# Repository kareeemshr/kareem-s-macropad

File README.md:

# kareem-s-macropad
My own macro pad to use to boost my coding productivity also my first actual project involving pcb's and 3d printed parts
im not really good at naming stuf so here my name :) even tho the macropads ugly i still made it, it has 12 switches(including that of the rotary encoder) along with a 128x32 OLED display and a ec11 rotary encoder

**CAD MODEL**

**BOTTOM OF THE CASE**

**TOP OF THE CASE**

**PCB SCHEMATICS**

(ik it looks ugly but its my first time T-T)
**PCB**

**FIRMWARE**
for the firmware i just made it so that all the keys write letters,ill actually make them do something when/if i get the hardware(no the rotary encoder doesnt do anything for now other than its button writing a letter)

**this is all just three days of work with literally 0 experience before so like if it wasnt obvious now u know**

**BOM**
1x xiao rp2040
11x cherry mx switches 
1x ec11 rotary encoder
1x 0.91 128x32 OLED

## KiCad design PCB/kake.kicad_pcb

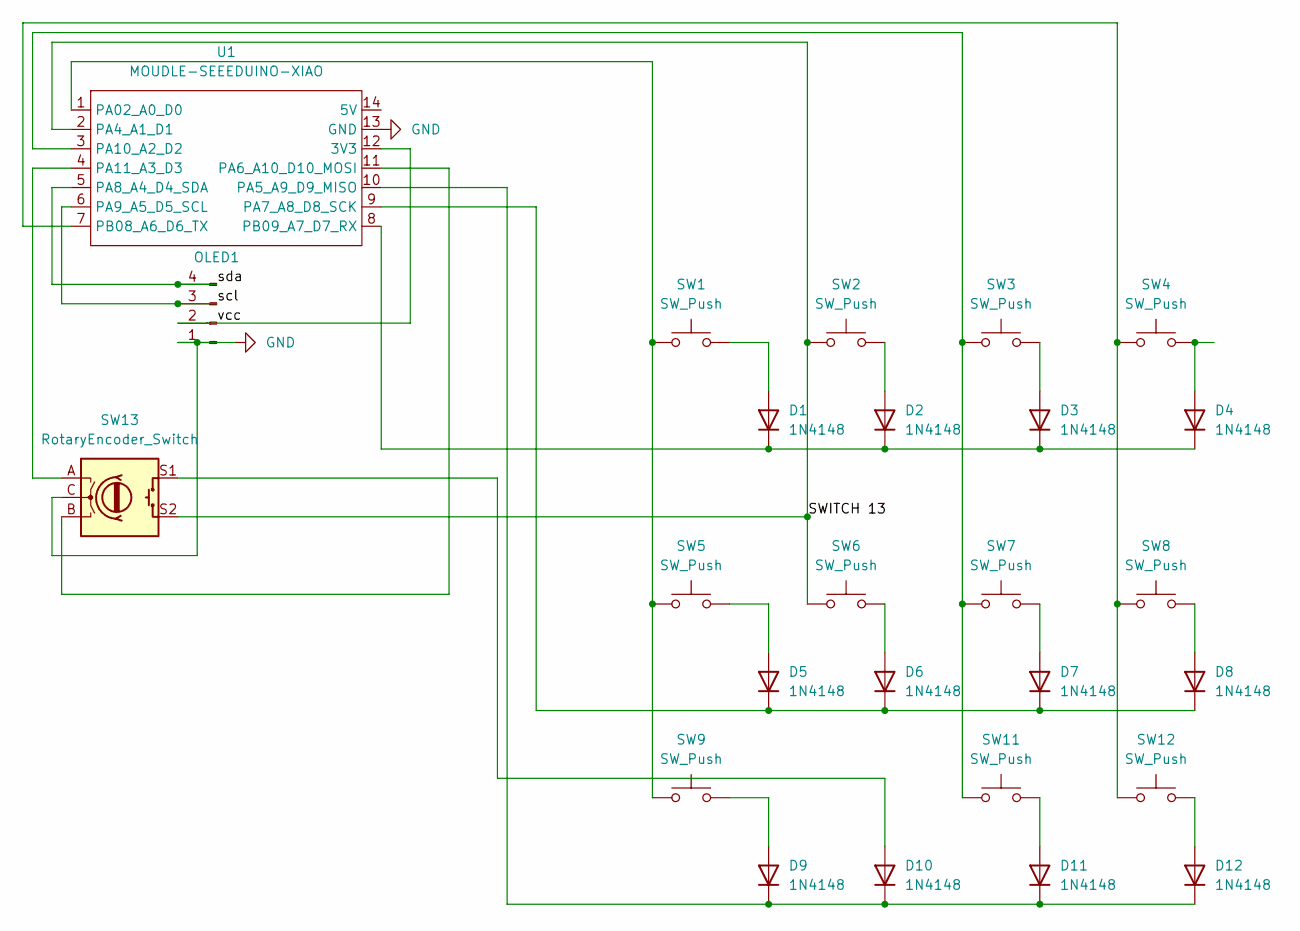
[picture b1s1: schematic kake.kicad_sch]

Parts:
D1, D2, D3, D4, D5, D6, D7, D8, D9, D10, D11, D12: 1N4148; D_DO-35_SOD27_P7.62mm_Horizontal
OLED1: Conn_01x04_Pin; SSD1306-0.91-OLED-4pin-128x32
SW1, SW2, SW3, SW4, SW5, SW6, SW7, SW8, SW9, SW11, SW12: SW_Push; SW_Cherry_MX_1.00u_PCB_3d
SW13: RotaryEncoder_Switch; RotaryEncoder_Alps_EC11E-Switch_Vertical_H20mm_CircularMoun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
U1: MOUDLE-SEEEDUINO-XIAO; XIAO-Generic-Hybrid-14P-2.54-21X17.8MM

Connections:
/scl: OLED1.3, U1.6 (PA9_A5_D5_SCL)
/sda: OLED1.4, U1.5 (PA8_A4_D4_SDA)
/vcc: OLED1.2, U1.12 (3V3)
GND: OLED1.1, SW13.C, U1.13 (GND)
unnamed: D1.2 (A), SW1.2
unnamed: D1.1 (K), D2.1 (K), D3.1 (K), D4.1 (K), U1.8 (PB09_A7_D7_RX)
unnamed: D2.2 (A), SW2.2
unnamed: D3.2 (A), SW3.2
unnamed: D4.2 (A), SW4.2
unnamed: D5.2 (A), SW5.2
unnamed: D5.1 (K), D6.1 (K), D7.1 (K), D8.1 (K), U1.9 (PA7_A8_D8_SCK)
unnamed: D6.2 (A), SW6.2
unnamed: D7.2 (A), SW7.2
unnamed: D8.2 (A), SW8.2
unnamed: D9.2 (A), SW9.2
unnamed: D10.2 (A), SW13.S1
unnamed: D9.1 (K), D10.1 (K), D11.1 (K), D12.1 (K), U1.10 (PA5_A9_D9_MISO)
unnamed: D11.2 (A), SW11.2
unnamed: D12.2 (A), SW12.2
unnamed: SW1.1, SW5.1, SW9.1, U1.1 (PA02_A0_D0)
unnamed: SW2.1, SW6.1, SW13.S2, U1.2 (PA4_A1_D1)
unnamed: SW13.B, U1.11 (PA6_A10_D10_MOSI)
unnamed: SW3.1, SW7.1, SW11.1, U1.3 (PA10_A2_D2)
unnamed: SW13.A, U1.4 (PA11_A3_D3)
unnamed: SW4.1, SW8.1, SW12.1, U1.7 (PB08_A6_D6_TX)

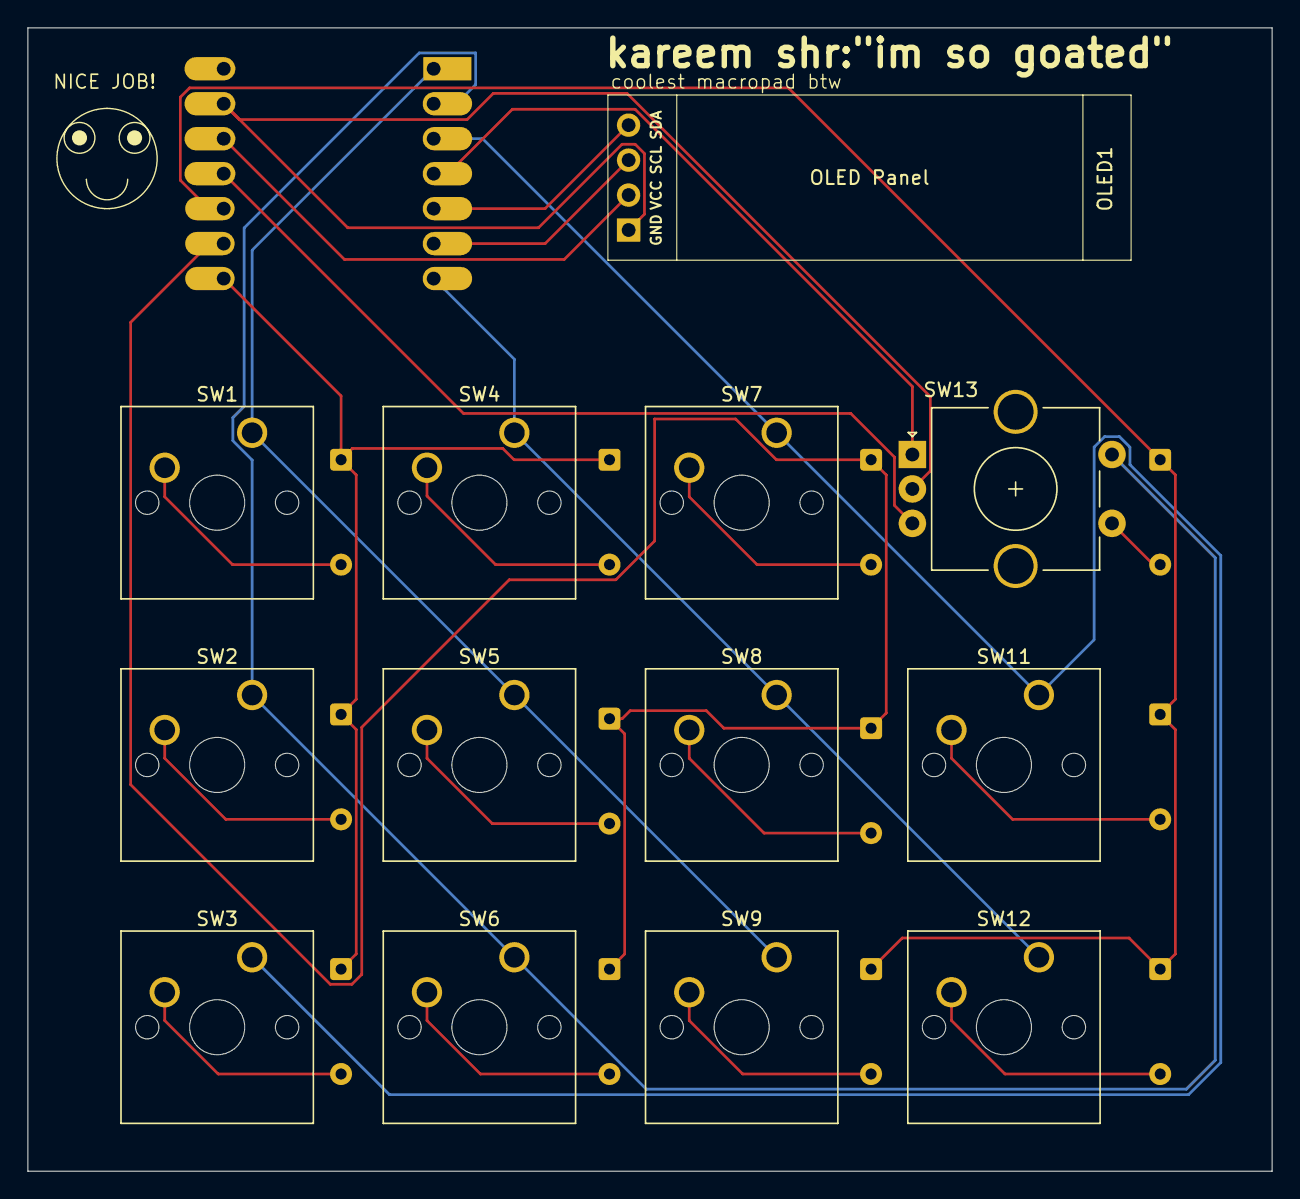
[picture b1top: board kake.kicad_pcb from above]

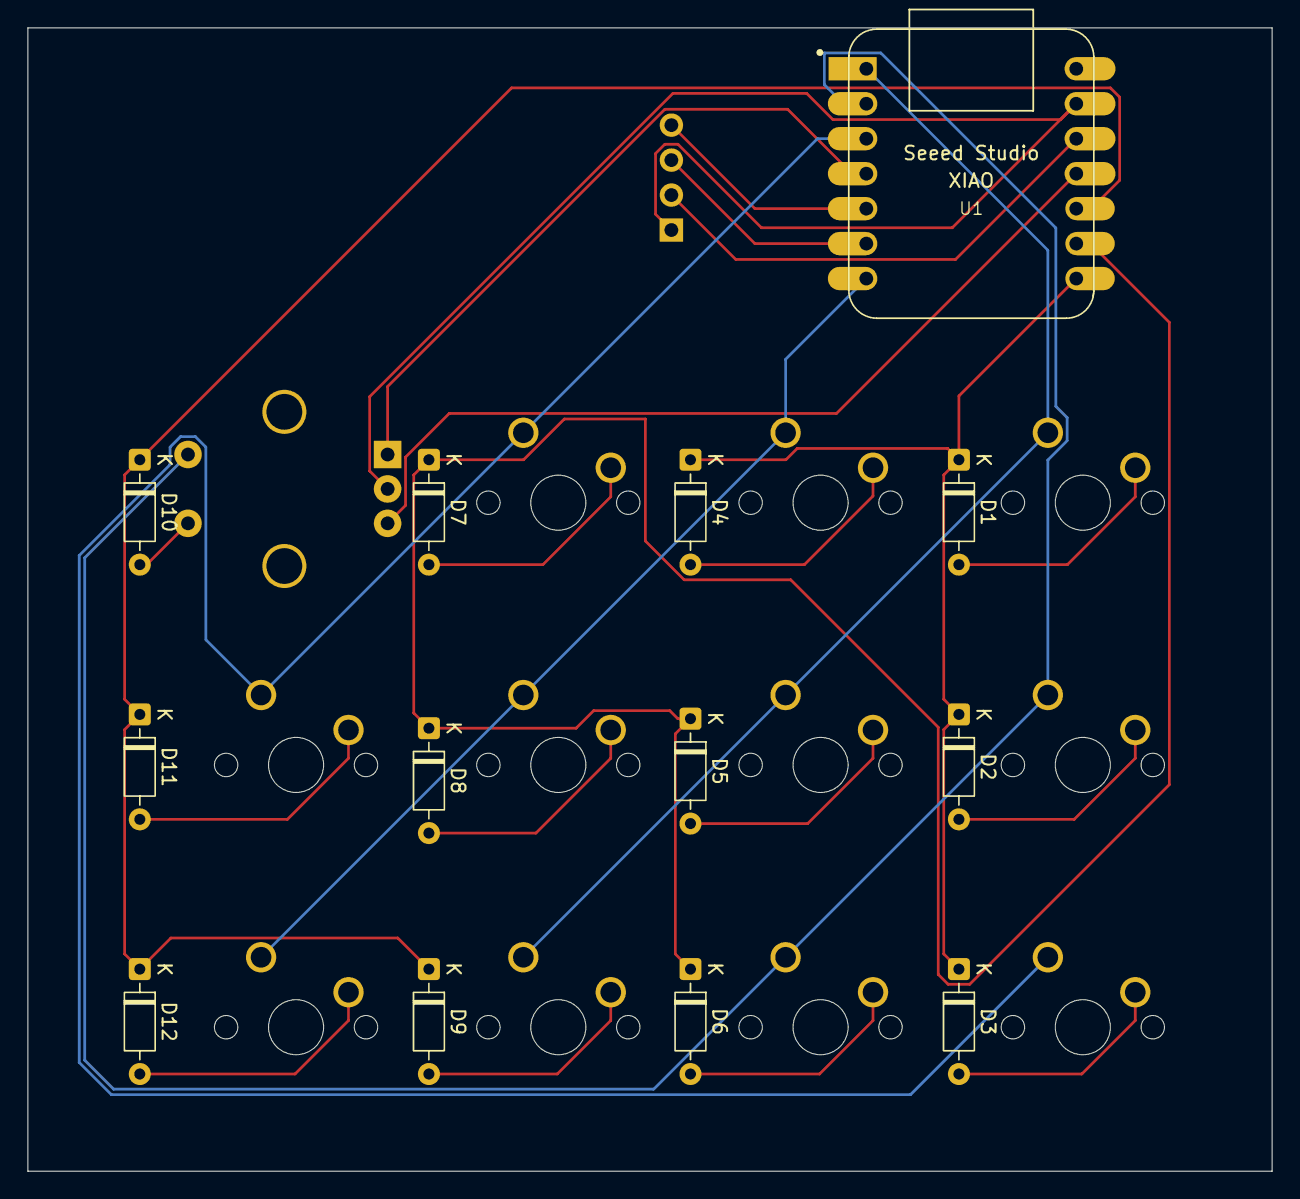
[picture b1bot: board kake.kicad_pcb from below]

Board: 2 copper layers, 90.4 x 83.1 mm, 26 parts (13 on the bottom side), 25 nets.

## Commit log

2026-02-28 actually updated the files
2026-02-28 Enhance README with project details and images
    Added detailed project description, images, and firmware notes.
2026-02-28 Update README with firmware details and personal note
    Clarified firmware functionality and added personal note on experience.
2026-03-01 Fix OLED display resolution and add BOM section
    Updated OLED display resolution in project description and added BOM.
2026-03-04 i think i added everything now
2026-03-04 Fix BOM.csv formatting by adding missing header
2026-03-04 Remove 'final price' column from BOM.csv
    Removed 'final price' column from BOM.csv.
2026-03-04 Fix formatting in BOM.csv
    Removed trailing commas and ensured proper formatting.
2026-03-05 Replace old image links with new ones
    Updated images in the README to new asset links.
